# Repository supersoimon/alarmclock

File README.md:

# ALARM CLOCK
This is a custom alarm clock based off of an ESP32C3, and a generic buzzer.

# Parts
It uses 6 Cherry MX keyswitches with custom 3d-printed keycaps, a buzzer, a XIAO SEEED ESP32C3, and a 2.25in TFT screen

# CAD
The CAD for this project is done on onshape. It has 3 shells, a bottom slip, and 3 different types of buttons. 

# FIRMWARE
This project is coded in the Arduino IDE. An .ino file is attached. 

# PCB
The PCB for this project was designed in KiCAD. It uses 1.6mm FR4 from JLCPCB. <br>

# BOM
| Name | Count | Cost (USD) | Link | Notes |
| :--- | :---: | :---: | :---: | :--- |
| Screen | 1 | \$0.00 | n/a | BLARE kit |
| Seeed XIAO ESP32C3 | 1 | \$0.00 | n/a | BLARE kit |
| Keyboard Switches | 12 | \$0.00 | n/a | BLARE kit |
| Buzzer | 1 | \$0.00 | n/a | BLARE kit |
| Screws & Heatset Inserts | 1 | \$0.00 | n/a | BLARE Kit |
| PCB | 1 | \$8.20 | n/a | Upload Gerbers to JLCPCB |
| PCB Shipping | 1 | \$7.36 |  | Will change depending on location |
| 3DP parts | 1 | \$0.00 | n/a |  |
| **Total** | | **\$15.56** | | |

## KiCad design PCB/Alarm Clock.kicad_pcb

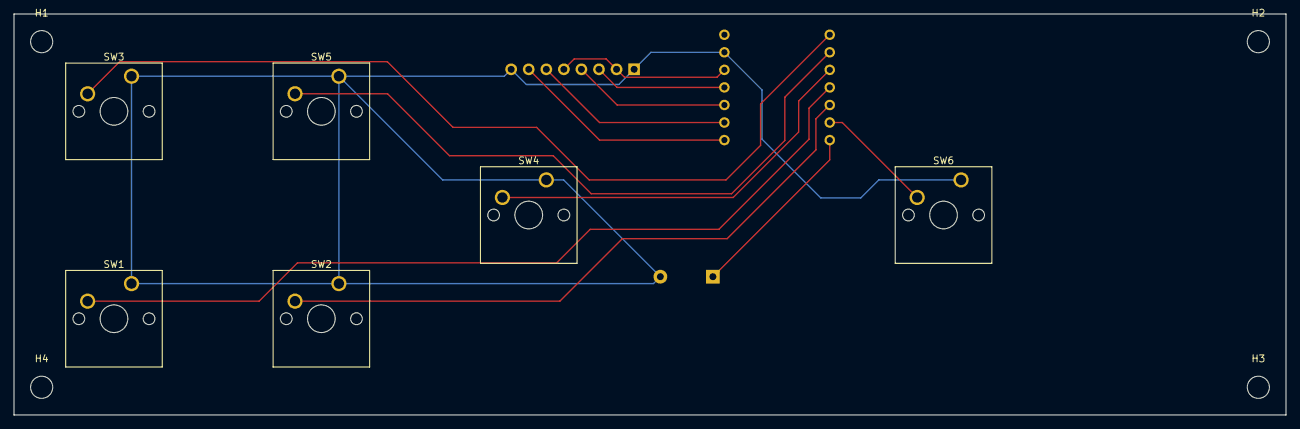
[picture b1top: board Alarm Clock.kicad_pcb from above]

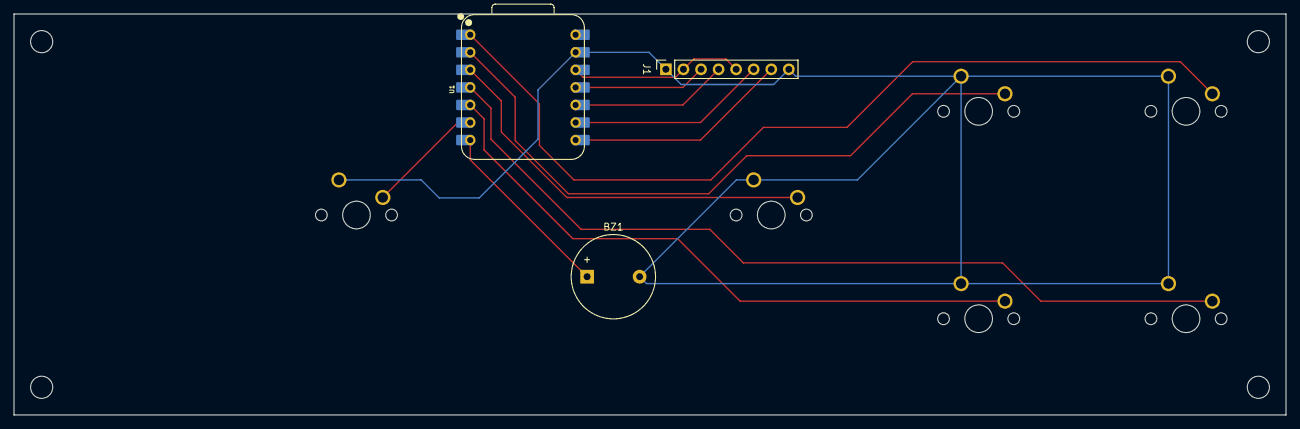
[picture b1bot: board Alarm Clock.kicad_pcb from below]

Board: 2 copper layers, 184.0 x 58.0 mm, 13 parts (3 on the bottom side), 13 nets.

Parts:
BZ1: Buzzer; Buzzer_12x9.5RM7.6
H1, H2, H3, H4: MountingHole; MountingHole_3.2mm_M3
J1: Conn_01x08_Pin; PinSocket_1x08_P2.54mm_Vertical
SW1, SW2, SW3, SW4, SW5, SW6: SW_Push; SW_Cherry_MX_1.00u_PCB
U1: XIAO-ESP32-C3-SMD; XIAO-ESP32-C3-DIP

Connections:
+3V3: J1.2, J1.5, U1.12 (3V3_OUT)
/buzzerin: BZ1.1 (+), U1.7 (D6)
/cs: J1.7, U1.8 (D7)
/dc: J1.6, U1.9 (D8)
/scl: J1.3, U1.11 (D10)
/sda: J1.4, U1.10 (D9/BOOT)
/sw0: SW1.2, U1.4 (D3)
/sw1: SW2.2, U1.5 (D4)
/sw2: SW3.2, U1.1 (D0)
/sw3: SW4.2, U1.3 (D2)
/sw4: SW5.2, U1.2 (D1)
/sw5: SW6.2, U1.6 (D5)
GND: BZ1.2 (-), J1.1, J1.8, SW1.1, SW2.1, SW3.1, SW4.1, SW5.1, SW6.1, U1.13 (GND)
